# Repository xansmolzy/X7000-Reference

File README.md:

# X7000-Reference
Wavetek 7000 inspired voltage reference on the cheap.

## As any FOSS thing operation and specs not guaranteed
## BOM list
-  The * denounces that these parts were used in development and there is probably a better alternative.
-  **(G)** denotes this is a generic part and nearly any alternative will do.

**⚠️For V0.1 and V0.2 RCur 124Ohm and 31.2Ohm were used, based on [work](https://xdevs.com/article/b7000/) 100Ohm and 18.2Ohm are encouraged but not tested⚠️**
**⚠️LTZ-A has oscillations in the order of 100uV⚠️**

If you like to stick to tested use 124 and 31.2Ohm respectively, when V0.3 gets assembled 100 and 18.2Ohm resistors will be used and data will be provided.

| Part name          | Manufacturer      | Quantity   | Price per (eur) | Notes                                                                   |
|:-------------------|:-----------------:|:----------:|:---------------:|------------------------------------------------------------------------:|
| NOMCT16031003AT1   | Vishay            |     1      |      3,64       |                                                                         |
| NOMCT16032001AT1   | Vishay            |     2      |      3,42       |                                                                         |
|--------------------|-------------------|------------|-----------------|                                                                         |
| Y0785100R000T9L    | Vishay            |     1      |      21,53      | RCur, can be 120 for less drift with more noise, RComp needs changed    |
| PTF5621R000BYEK    | Vishay            |     1*     |      5,11       | (or better more satble resistor) RComp                                  |
| TNPW0402137RBEED   | Vishay            |     1*     |      0,67       | RComp trim to 18,18 Ohm for 100Ohms RCur                                |
|--------------------|-------------------|------------|-----------------|                                                                         |
| ADA4523-1BRZ       | Analog Devices    |     4      |      2,65       |                                                                         |
| LTZ1000CH#PBF      | Analog Devices    |     1      |      68,9       | Or LTZ1000ACH#PBF or ADR (untested)                                     |
| 1N4148UR-1         | Microchip         |     2(G)   |      0,81       |                                                                         |
| CRT1206-DY-1004ELF | Bourns            |     1(G)   |      0,35       |                                                                         |
| CRT1206-BY-1002EST | Bourns            |     1(G)   |      0,35       |                                                                         |
| CRT1206-BY-1001ELF | Bourns            |     1(G)   |      0,52       |                                                                         |
| CRT1206-BY-1002EST | Bourns            |     1(G)   |      0,35       |                                                                         |
| ERA-8AED302V       | Panasonic         |     1(G)   |      0,46       |                                                                         |
| ERA-8AEB4223V      | Panasonic         |     1(G)   |      0,58       |                                                                         |
| C1206C104K5RAC7867 | Kemet             |      4     |      0,12       |                                                                         |
| C1206X103K5RECAUT  | Kemet             |      1     |      0,44       |                                                                         |         
| 1206YC223MAT2A     | Kyocera           |      1     |      0,26       |                                                                         |
| SPZT3904T1G        | Onsemi            |      1     |      0,64       |                                                                         |
| **TOTAL**          |-------------------|------------|      1--,28     |                                                                         |

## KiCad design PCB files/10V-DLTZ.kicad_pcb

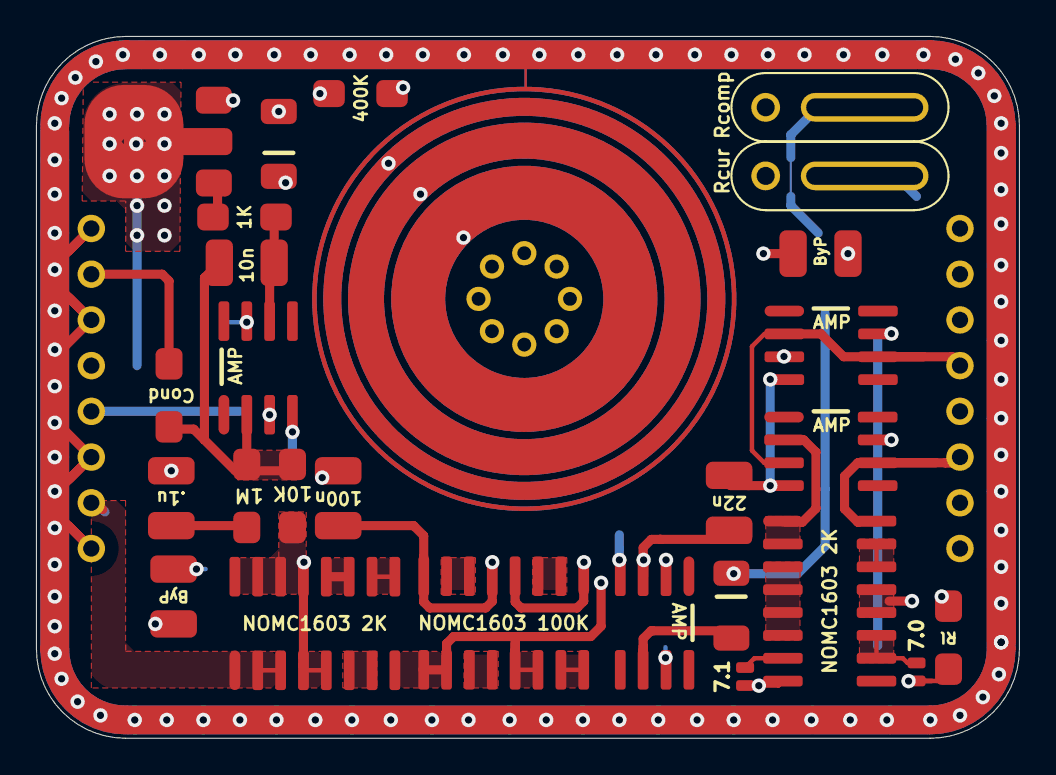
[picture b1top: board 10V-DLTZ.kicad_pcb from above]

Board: 4 copper layers, 54.6 x 39.0 mm, 29 parts (0 on the bottom side), 32 nets.

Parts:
C1, C2, C3, C4, C5, C6: Capacitor; 1210
D1, D2: 1N4148
J1, J2: SolderJumper
J4, J5: 8x1; 5x1
R1, R2, R3, R4, R5, R8: RES; 1206
Rcomp: PrecRes
Rcur: PrecRes
Rn1: NOMC1603 100K; SOIC-16
Rn2: NOMC1603 2K; SOIC-16
Rn3: NOMC1603; SOIC-16
SZ1: LTZ1000; TO5-8
U1, U2, U7, U9: ADA4523-1; SOIC-8
U3: NPN-Transistor; PZT3904

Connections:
GNDPWR: C3.1, C4.1, C5.1, C6.1, D1.2, J5.1, J5.3, J5.6, J5.8, U1.4, U2.4, U7.4, U9.4
unnamed: C1.1, R3.1
unnamed: C1.2, R1.2
unnamed: C2.1, R5.2, U9.6
unnamed: C2.2, R1.1, R2.2, R4.1, U9.2
unnamed: C3.2, Rn1.5, Rn1.8, SZ1.8, U9.3
unnamed: C4.2, Rn1.1, Rn1.4, SZ1.5, U7.3
unnamed: D1.1, SZ1.2
unnamed: D2.1, U7.6
unnamed: J1.2, Rn3.7
unnamed: J2.2, Rn3.10, Rn3.11
unnamed: J4.4, R8.2, U1.3, U2.2, U2.6
unnamed: J4.6, Rn3.16, U1.6
unnamed: J5.2, R4.2
unnamed: R2.1, Rn2.4, Rn2.5, Rn2.13, Rn2.14, Rn2.15, Rn2.16, SZ1.6
unnamed: R3.2, Rcur.1, SZ1.4, U7.2
unnamed: R5.1, U3.1
unnamed: Rn1.2, Rn1.3
unnamed: Rn1.6, Rn1.7
unnamed: Rn1.11, Rn1.12
unnamed: Rn1.15, Rn1.16
unnamed: Rn2.6, Rn2.7
unnamed: Rn2.9, Rn2.10
unnamed: Rn2.11, Rn2.12
unnamed: Rn3.1, Rn3.2, U1.2
unnamed: Rn3.3, Rn3.4, Rn3.5, Rn3.6
unnamed: Rn3.14, Rn3.15
unnamed: SZ1.1, U3.3
Sense+: J4.2, Rcomp.1, SZ1.3, U2.3
Sense-: J1.1, J2.1, J4.3, J4.5, J4.7, J5.7, R8.1, Rcur.2, Rn2.1, Rn2.2, Rn2.3, Rn3.8, Rn3.9, Rn3.12, Rn3.13, SZ1.7
VPP: C5.2, C6.2, J5.5, U1.7, U2.7, U3.2, U7.7, U9.7
VSSA: D2.2, Rcomp.2, Rn1.9, Rn1.10, Rn1.13, Rn1.14, Rn2.8

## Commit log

2022-03-03 Add images add readme
2022-11-11 Add PCB V0.2
